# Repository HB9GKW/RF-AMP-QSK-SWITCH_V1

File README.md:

# RF-AMP-CNTLR_V1
HB9GKW RF Amplifier QSK TX-RX PIN switch

Features:
- low loss high power (3kW) handling
- high VSWR ruggedness
- high isolation
- fail-save with sequencer readback

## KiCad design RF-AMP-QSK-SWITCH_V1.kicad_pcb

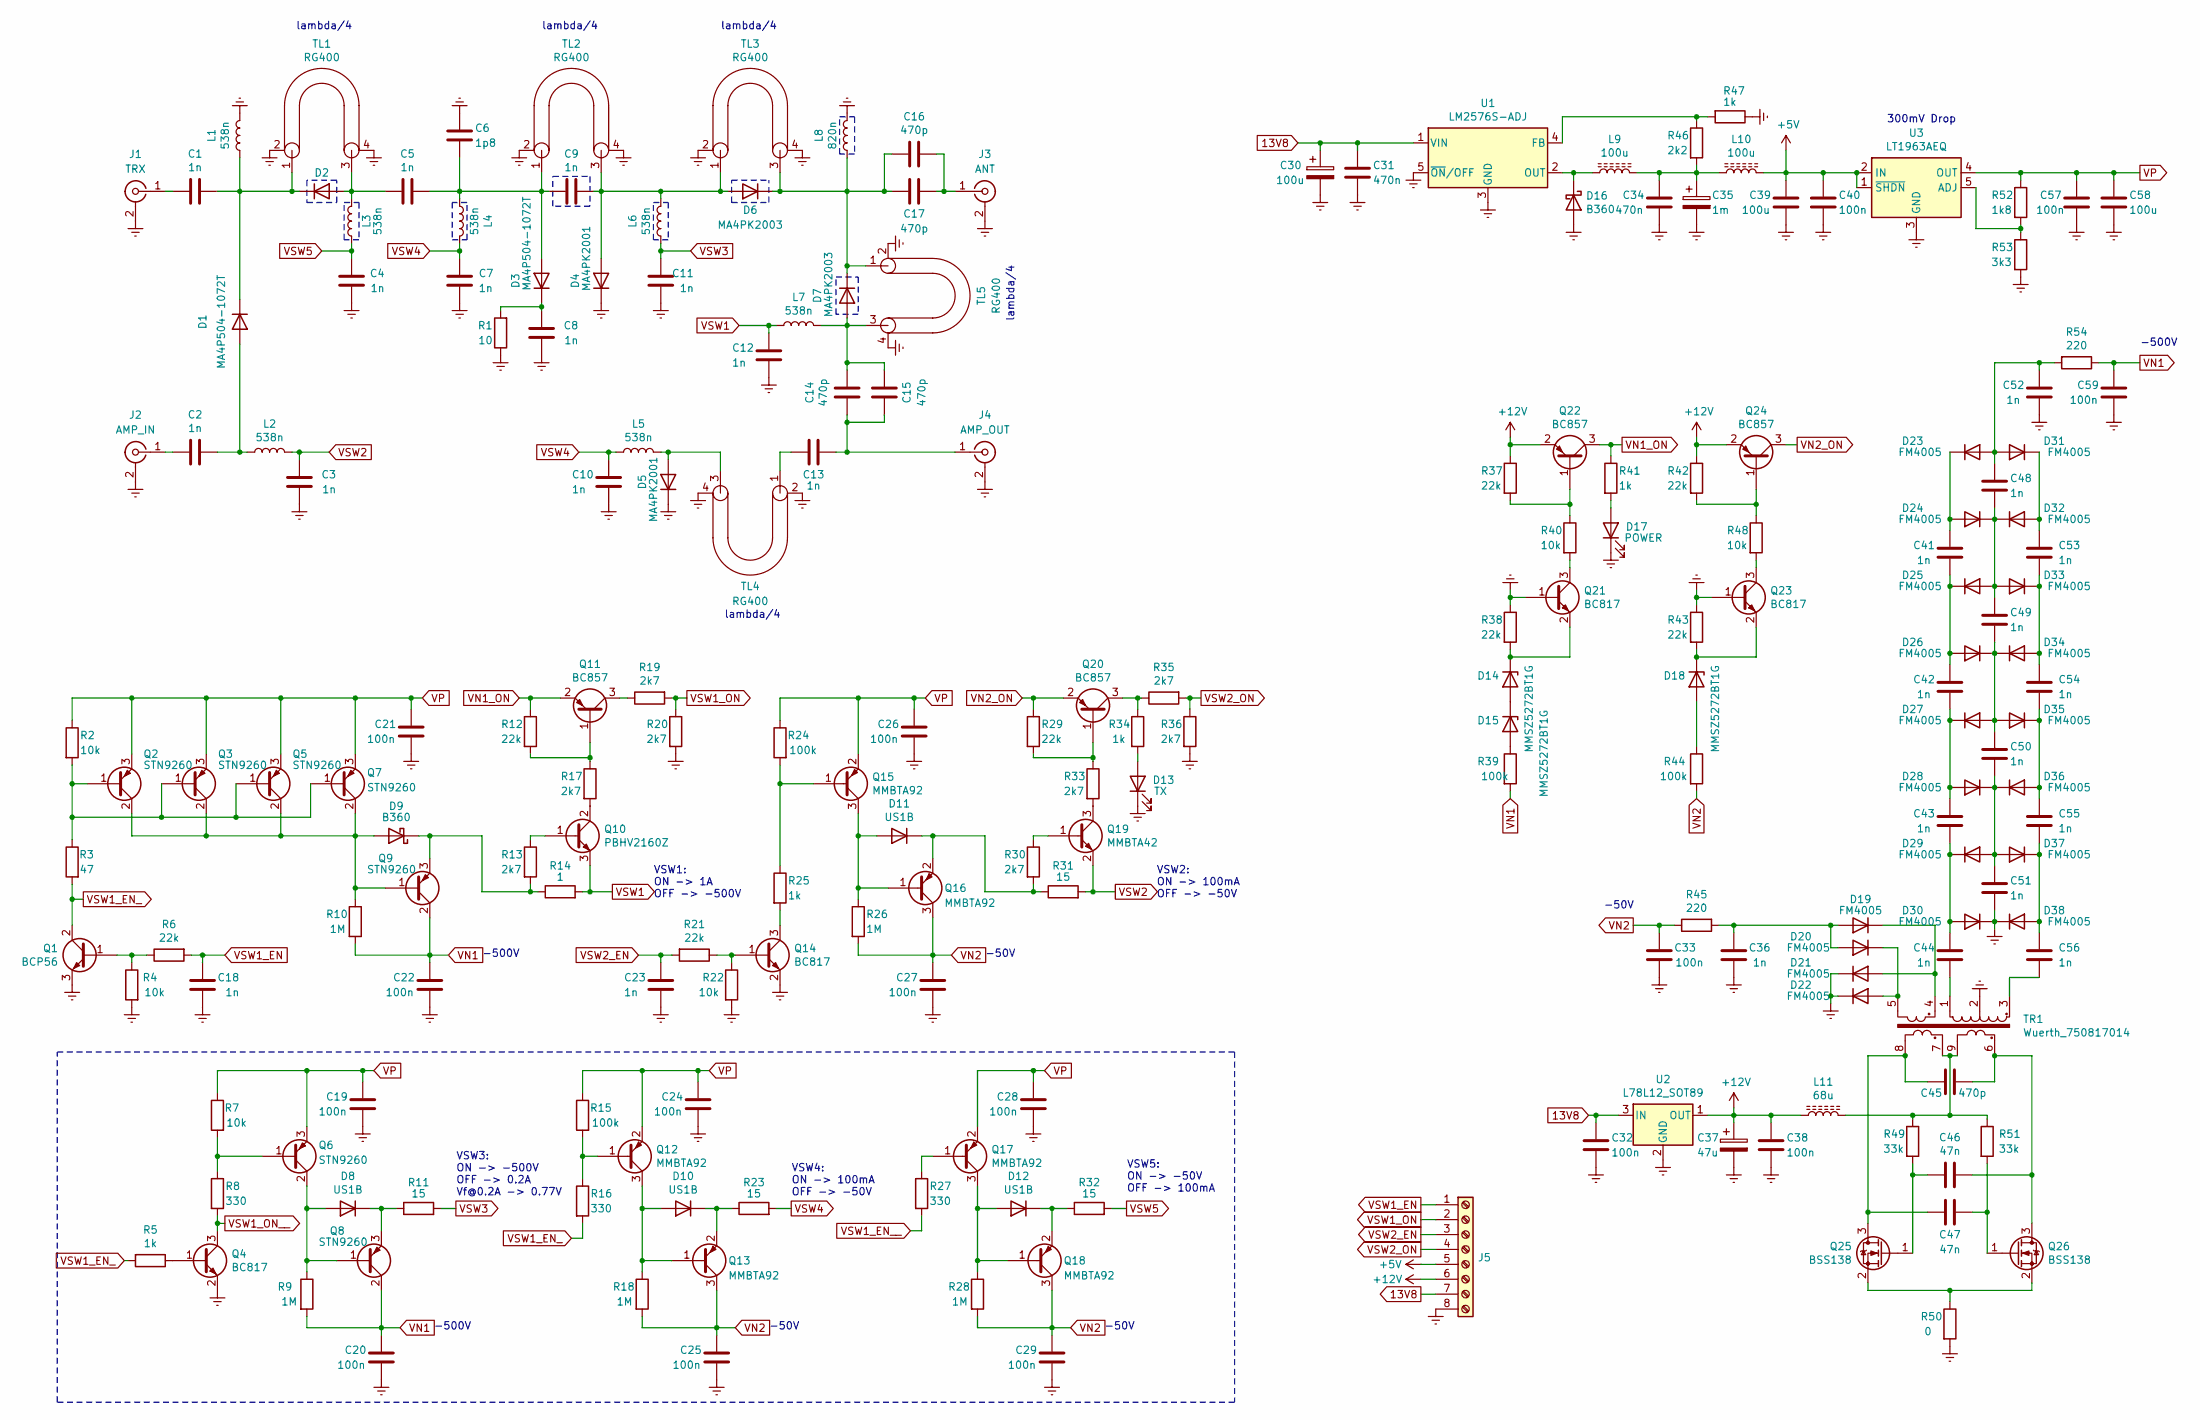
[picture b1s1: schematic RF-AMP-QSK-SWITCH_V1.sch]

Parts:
C1, C2, C3, C4, C5, C7, C8, C9, C10, C11, C12, C13: 1n; C_1210_3225Metric
C6: 1p8; C_1210_3225Metric
C14, C15, C16, C17: 470p; C_1210_3225Metric
C18, C23: 1n; C_0805_2012Metric
C19, C21, C24, C25, C26, C27, C28, C29, C32, C38, C40, C57: 100n; C_0805_2012Metric
C20, C22, C33, C59: 100n; C_1206_3216Metric
C30: 100u; CP_Elec_10x10
C31, C34: 470n; C_0805_2012Metric
C35: 1m; CP_Elec_10x10
C36, C41, C42, C43, C44, C48, C49, C50, C51, C52, C53, C54, C55, C56: 1n; C_1206_3216Metric
C37: 47u; CP_Elec_10x10
C39, C58: 100u; C_1210_3225Metric
C45: 470p; C_0805_2012Metric
C46, C47: 47n; C_0805_2012Metric
D1, D2, D3: MA4P504-1072T; D_1210_3225Metric
D4, D5: MA4PK2001; MA4PK200x
D6, D7: MA4PK2003; MA4PK200x
D8, D10, D11, D12: US1B; D_SMA
D9, D16: B360; D_SMC
D13: TX; LED_D3.0mm
D14, D15, D18: MMSZ5272BT1G; D_SOD-123
D17: POWER; LED_D3.0mm
D19, D20, D21, D22, D23, D24, D25, D26, D27, D28, D29, D30, D31, D32, D33, D34, D35, D36, D37, D38: FM4005; D_SMA
J1: TRX; N_connector_panel_small_flange
J2: AMP_IN; N_connector_panel_small_flange
J3: ANT; N_connector_panel_small_flange
J4: AMP_OUT; N_connector_panel_small_flange
J5: Screw_Terminal_01x08; TerminalBlock_Phoenix_MPT-0,5-8-2.54_1x08_P2.54mm_Horizontal
L1, L2, L3, L4, L5, L6, L7: 538n; Coilcraft_Maxi_Spring
L8: 820n; Coilcraft_Maxi_Spring
L9, L10: 100u; L_Bourns_SRR1210A
L11: 68u; L_1210_3225Metric
Q1: BCP56; SOT-223-3_TabPin2
Q2, Q3, Q5, Q6, Q7, Q8, Q9: STN9260; SOT-223-3_TabPin2
Q4, Q14, Q21, Q23: BC817; SOT-23
Q10: PBHV2160Z; SOT-223-3_TabPin2
Q11, Q20, Q22, Q24: BC857; SOT-23
Q12, Q13, Q15, Q16, Q17, Q18: MMBTA92; SOT-23
Q19: MMBTA42; SOT-23
Q25, Q26: BSS138; SOT-23
R1: 10; R_1206_3216Metric
R2, R4, R7, R22, R40, R48: 10k; R_0805_2012Metric
R3: 47; R_1206_3216Metric
R5, R25, R34, R41, R47: 1k; R_0805_2012Metric
R6, R12, R21, R29, R37, R38, R42, R43: 22k; R_0805_2012Metric
R8, R16, R27: 330; R_0805_2012Metric
R9, R10, R18, R26, R28: 1M; R_0805_2012Metric
R11, R23, R31, R32: 15; R_2512_6332Metric
R13, R17, R19, R20, R30, R33, R35, R36: 2k7; R_0805_2012Metric
R14: 1; R_Shunt_Vishay_WSR2_WSR3
R15, R24, R39, R44: 100k; R_0805_2012Metric
R45, R54: 220; R_0805_2012Metric
R46: 2k2; R_0805_2012Metric
R49, R51: 33k; R_0805_2012Metric
R50: 0; R_0805_2012Metric
R52: 1k8; R_0805_2012Metric
R53: 3k3; R_0805_2012Metric
TL1, TL2, TL3, TL4, TL5: RG400
TR1: Wuerth_750817014; Transformer_Wuerth_750817014
U1: LM2576S-ADJ; TO-263-5_TabPin3
U2: L78L12_SOT89; SOT-89-3
U3: LT1963AEQ; TO-263-5_TabPin3

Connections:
13V8: C30.1, C31.2, C32.2, J5.7, U1.1 (VIN), U2.3 (IN)
+5V: C39.2, C40.2, J5.5, L10.2, U3.1 (~SHDN), U3.2 (IN)
+12V: C37.1, C38.2, J5.6, L11.1, Q22.2 (E), Q24.2 (E), R37.1, R42.1, U2.1 (OUT)
Earth: C3.1, C4.1, C6.1, C7.1, C8.1, C10.1, C11.1, C12.1, C18.1, C19.1, C20.1, C21.1, C22.1, C23.1, C24.1, C25.1, C26.1, C27.1, C28.1, C29.1, C30.2, C31.1, C32.1, C33.1, C34.1, C35.2, C36.1, C37.2, C38.1, C39.1, C40.1, C51.1, C52.1, C57.1, C58.1, C59.1, D4.1 (K), D5.1 (K), D13.1 (K), D16.2 (A), D17.1 (K), D21.1 (K), D22.1 (K), D30.1 (K), D38.1 (K), J1.2 (Ext), J2.2 (Ext), J3.2 (Ext), J4.2 (Ext), J5.8, L1.2, L8.2, Q1.3 (E), Q4.2 (E), Q14.2 (E), Q21.1 (B), Q23.1 (B), R1.1, R4.2, R20.2, R22.2, R36.2, R38.1, R43.1, R47.1, R50.2, R53.2, TL1.2 (OC1), TL1.4 (OC2), TL2.2 (OC1), TL2.4 (OC2), TL3.2 (OC1), TL3.4 (OC2), TL4.2 (OC1), TL4.4 (OC2), TL5.2 (OC1), TL5.4 (OC2), TR1.2, U1.3 (GND), U1.5 (~ON~/OFF), U2.2 (GND), U3.3 (GND); also elsewhere on the board
unnamed: C1.1, D1.1 (K), D2.1 (K), L1.1, TL1.1 (IC1)
unnamed: C1.2, J1.1 (In)
unnamed: C2.1, D1.2 (A), L2.2
unnamed: C2.2, J2.1 (In)
unnamed: C5.1, C6.2, C9.2, D3.2 (A), L4.2, TL2.1 (IC1)
unnamed: C5.2, D2.2 (A), L3.2, TL1.3 (IC1)
unnamed: C8.2, D3.1 (K), R1.2
unnamed: C9.1, D4.2 (A), D6.2 (A), L6.2, TL2.3 (IC1), TL3.1 (IC1)
unnamed: C13.1, TL4.1 (IC1)
unnamed: C13.2, C14.1, C15.1, J4.1 (In)
unnamed: C14.2, C15.2, D7.2 (A), L7.2, TL5.3 (IC1)
unnamed: C16.1, C17.1, D6.1 (K), D7.1 (K), L8.1, TL3.3 (IC1), TL5.1 (IC1)
unnamed: C16.2, C17.2, J3.1 (In)
unnamed: C34.2, C35.1, L9.2, L10.1, R46.2
unnamed: C36.2, D19.2 (A), D20.2 (A), R45.2
unnamed: C41.1, C42.2, D25.1 (K), D26.2 (A)
unnamed: C41.2, D23.1 (K), D24.2 (A)
unnamed: C42.1, C43.2, D27.1 (K), D28.2 (A)
unnamed: C43.1, C44.2, D29.1 (K), D30.2 (A)
unnamed: C44.1, TR1.1
unnamed: C45.1, C46.1, Q26.3 (D), TR1.6
unnamed: C45.2, C47.2, Q25.3 (D), TR1.8
unnamed: C46.2, Q25.1 (G), R49.2
unnamed: C47.1, Q26.1 (G), R51.2
unnamed: C48.1, C49.2, D24.1 (K), D25.2 (A), D32.1 (K), D33.2 (A)
unnamed: C48.2, C52.2, D23.2 (A), D31.2 (A), R54.2
unnamed: C49.1, C50.2, D26.1 (K), D27.2 (A), D34.1 (K), D35.2 (A)
unnamed: C50.1, C51.2, D28.1 (K), D29.2 (A), D36.1 (K), D37.2 (A)
unnamed: C53.1, C54.2, D33.1 (K), D34.2 (A)
unnamed: C53.2, D31.1 (K), D32.2 (A)
unnamed: C54.1, C55.2, D35.1 (K), D36.2 (A)
unnamed: C55.1, C56.2, D37.1 (K), D38.2 (A)
unnamed: C56.1, TR1.3
unnamed: D5.2 (A), L5.2, TL4.3 (IC1)
unnamed: D8.1 (K), Q8.3 (E), R11.1
unnamed: D8.2 (A), Q6.2 (C), Q8.1 (B), R9.1
unnamed: D9.1 (K), Q9.3 (E), R13.2, R14.1
unnamed: D9.2 (A), Q2.2 (C), Q3.2 (C), Q5.2 (C), Q7.2 (C), Q9.1 (B), R10.1
unnamed: D10.1 (K), Q13.2 (E), R23.1
unnamed: D10.2 (A), Q12.3 (C), Q13.1 (B), R18.1
unnamed: D11.1 (K), Q16.2 (E), R30.2, R31.1
unnamed: D11.2 (A), Q15.3 (C), Q16.1 (B), R26.1
unnamed: D12.1 (K), Q18.2 (E), R32.1
unnamed: D12.2 (A), Q17.3 (C), Q18.1 (B), R28.1
unnamed: D13.2 (A), R34.2
unnamed: D14.1 (K), Q21.2 (E), R38.2
unnamed: D14.2 (A), D15.1 (K)
unnamed: D15.2 (A), R39.1
unnamed: D16.1 (K), L9.1, U1.2 (OUT)
unnamed: D17.2 (A), R41.2
unnamed: D18.1 (K), Q23.2 (E), R43.2
unnamed: D18.2 (A), R44.1
unnamed: D19.1 (K), D21.2 (A), TR1.4
unnamed: D20.1 (K), D22.2 (A), TR1.5
unnamed: L11.2, R49.1, R51.1, TR1.7, TR1.9
unnamed: Q1.1 (B), R4.1, R6.1
unnamed: Q2.1 (B), Q3.1 (B), Q5.1 (B), Q7.1 (B), R2.2, R3.1
unnamed: Q4.1 (B), R5.1
unnamed: Q6.1 (B), R7.2, R8.1
unnamed: Q10.1 (B), R13.1
unnamed: Q10.2 (C), R17.2
unnamed: Q11.1 (B), R12.2, R17.1
unnamed: Q11.3 (C), R19.1
unnamed: Q12.1 (B), R15.2, R16.1
unnamed: Q14.1 (B), R21.1, R22.1
unnamed: Q14.3 (C), R25.2
unnamed: Q15.1 (B), R24.2, R25.1
unnamed: Q17.1 (B), R27.1
unnamed: Q19.1 (B), R30.1
unnamed: Q19.3 (C), R33.2
unnamed: Q20.1 (B), R29.2, R33.1
unnamed: Q20.3 (C), R34.1, R35.1
unnamed: Q21.3 (C), R40.2
unnamed: Q22.1 (B), R37.2, R40.1
unnamed: Q23.3 (C), R48.2
unnamed: Q24.1 (B), R42.2, R48.1
unnamed: Q25.2 (S), Q26.2 (S), R50.1
unnamed: R46.1, R47.2, U1.4 (FB)
unnamed: R52.2, R53.1, U3.5 (ADJ)
VN1: C20.2, C22.2, C59.2, Q8.2 (C), Q9.2 (C), R9.2, R10.2, R39.2, R54.1
VN1_ON: Q11.2 (E), Q22.3 (C), R12.1, R41.1
VN2: C25.2, C27.2, C29.2, C33.2, Q13.3 (C), Q16.3 (C), Q18.3 (C), R18.2, R26.2, R28.2, R44.2, R45.1
VN2_ON: Q20.2 (E), Q24.3 (C), R29.1
VP: C19.2, C21.2, C24.2, C26.2, C28.2, C57.2, C58.2, Q2.3 (E), Q3.3 (E), Q5.3 (E), Q6.3 (E), Q7.3 (E), Q12.2 (E), Q15.2 (E), Q17.2 (E), R2.1, R7.1, R15.1, R24.1, R52.1, U3.4 (OUT)
VSW1: C12.2, L7.1, Q10.3 (E), R14.2
VSW1_EN: C18.2, J5.1, R6.2
VSW1_EN_: Q1.2 (C), Q1.4 (C), R3.2, R5.2, R16.2
VSW1_EN__: R27.2
VSW1_ON: J5.2, R19.2, R20.1
VSW1_ON__: Q4.3 (C), R8.2
VSW2: C3.2, L2.1, Q19.2 (E), R31.2
VSW2_EN: C23.2, J5.3, R21.2
VSW2_ON: J5.4, R35.2, R36.1
VSW3: C11.2, L6.1, R11.2
VSW4: C7.2, C10.2, L4.1, L5.1, R23.2
VSW5: C4.2, L3.1, R32.2

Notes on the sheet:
lambda/4
VSW1: ON -> 1A OFF -> -500V
VSW2: ON -> 100mA OFF -> -50V
-500V
300mV Drop
-50V
VSW3: ON -> -500V OFF -> 0.2A Vf@0.2A -> 0.77V
VSW5: ON -> -50V OFF -> 100mA
VSW4: ON -> 100mA OFF -> -50V

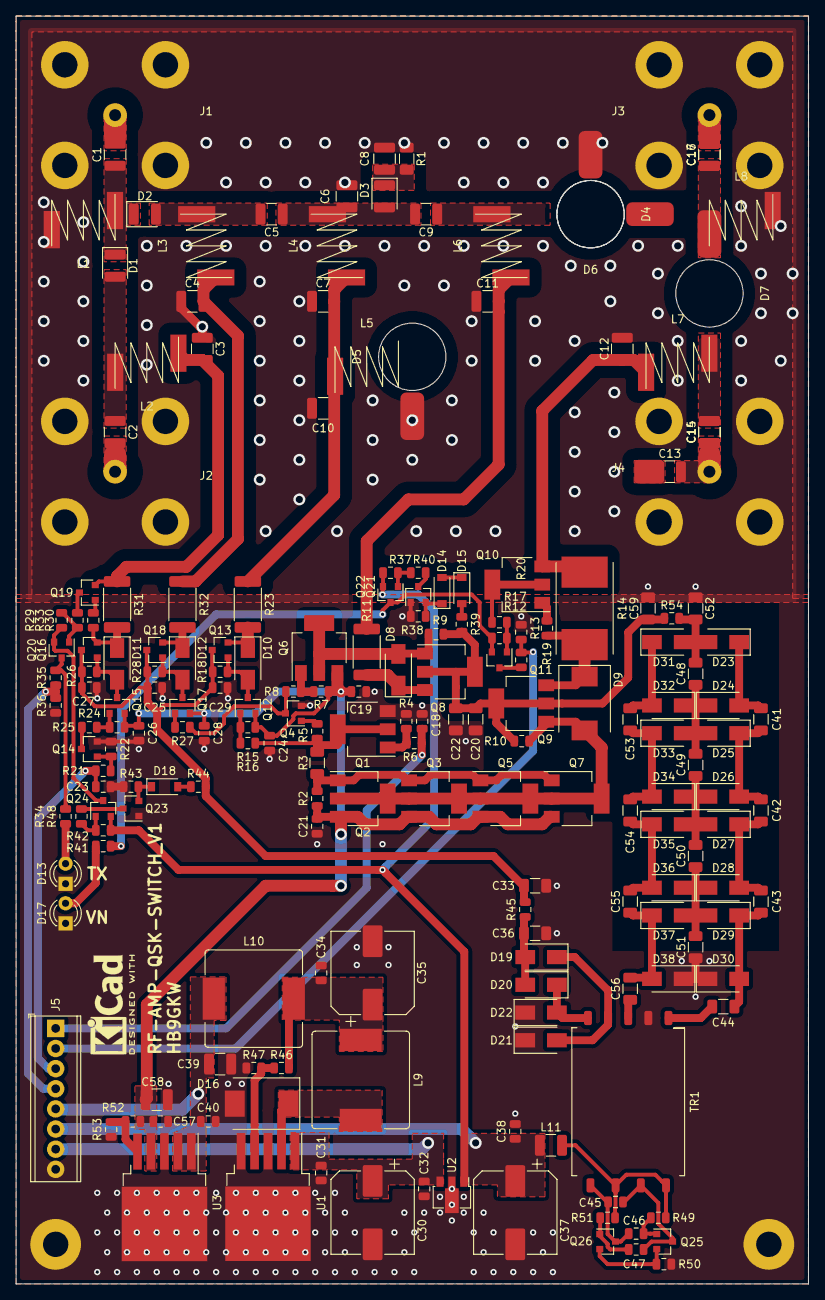
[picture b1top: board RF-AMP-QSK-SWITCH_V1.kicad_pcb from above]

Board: 2 copper layers, 100.0 x 160.0 mm, 199 parts (0 on the bottom side), 98 nets.

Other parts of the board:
MH1, MH2: MountingHole_3.2mm_M3_Pad

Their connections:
Earth: MH1.1, MH2.1; also elsewhere on the board

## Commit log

2020-07-09 final commit
2020-07-17 Revision1
